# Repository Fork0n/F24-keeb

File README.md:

# F24-keeb
#### ever wished to have or use a keyboard with 2!!! function rows? no? well it's here anyways! by having 2 function rows with F13-F24 keys + 5 macro keys + 2 dials you can now have up to 19* customizable keys! that's like a built in streamdeck! and all of that while never leaving your keyboard! 

*assuming you remap all 12 additional function keys + 5 macros + 2 dial on click

<!--  -->

## Project info:
### Format: TKL++
### Materials:
- case: matte Jet Black ABS
- (alt) case top: matte purple ABS
- plate: mate Ket Black Polyoxymethylene (POM)
- keycaps: to be decided
### Switches: Gateron PRO v3 BLACK or Gateron Smoothie Sea Salt
### Microcontroller: 3rd party Type C Pi Pico (RP2040)
### Firmware: Custom, RMK/QMK/VIAL based (WIP)
### Mounting Style: gasket mount

## Design files
available [https://github.com/Fork0n/F24-keeb/tree/main/production](here)

(source will be added later)

## Assembly 101

WIP WIP WIP WIP WIP WIP WIP WIP WIP

## Firmware 101

WIP WIP WIP WIP WIP WIP WIP WIP WIP

## CH I: the idea:
it all started when I got a new laptop with the nasty copilot key, at first i left it on seen and just occasionally missclicked it opening copilot, then i found out that power toys allow you to remap any key to any function (even virtual keys), that was great for muting myself on discord but i felt like i needed more. at approximately the same time i discovered that i can turn my laptop's numpad in a DIY streamdeck AKA macropad, that was still not enough. One time when i was watching a video by bringus studious i took a closer look at the infamous _dirty cherry keyboard_, instead of a mono top row it was doubled! taking and EVEN closer look revealed that the keyboard had the row folded instead of a double row. Anyways that was the time when a "double function row keyboard" idea was born.

## Project Updates & Devlogs
Check out our detailed progress and updates in the [DEVLOGS.md](./DEVLOGS.md)!

> <small>**Project Info & Licensing**  
> Designed by **@forkosssa** ([Contact/Portfolio](https://large-type.com/#TODO)) • Licensed under [CC BY 4.0](LICENSE).  
> *All physical derivative PCBs must retain original author branding on silkscreen layers as outlined in Section 3(a).*</small>

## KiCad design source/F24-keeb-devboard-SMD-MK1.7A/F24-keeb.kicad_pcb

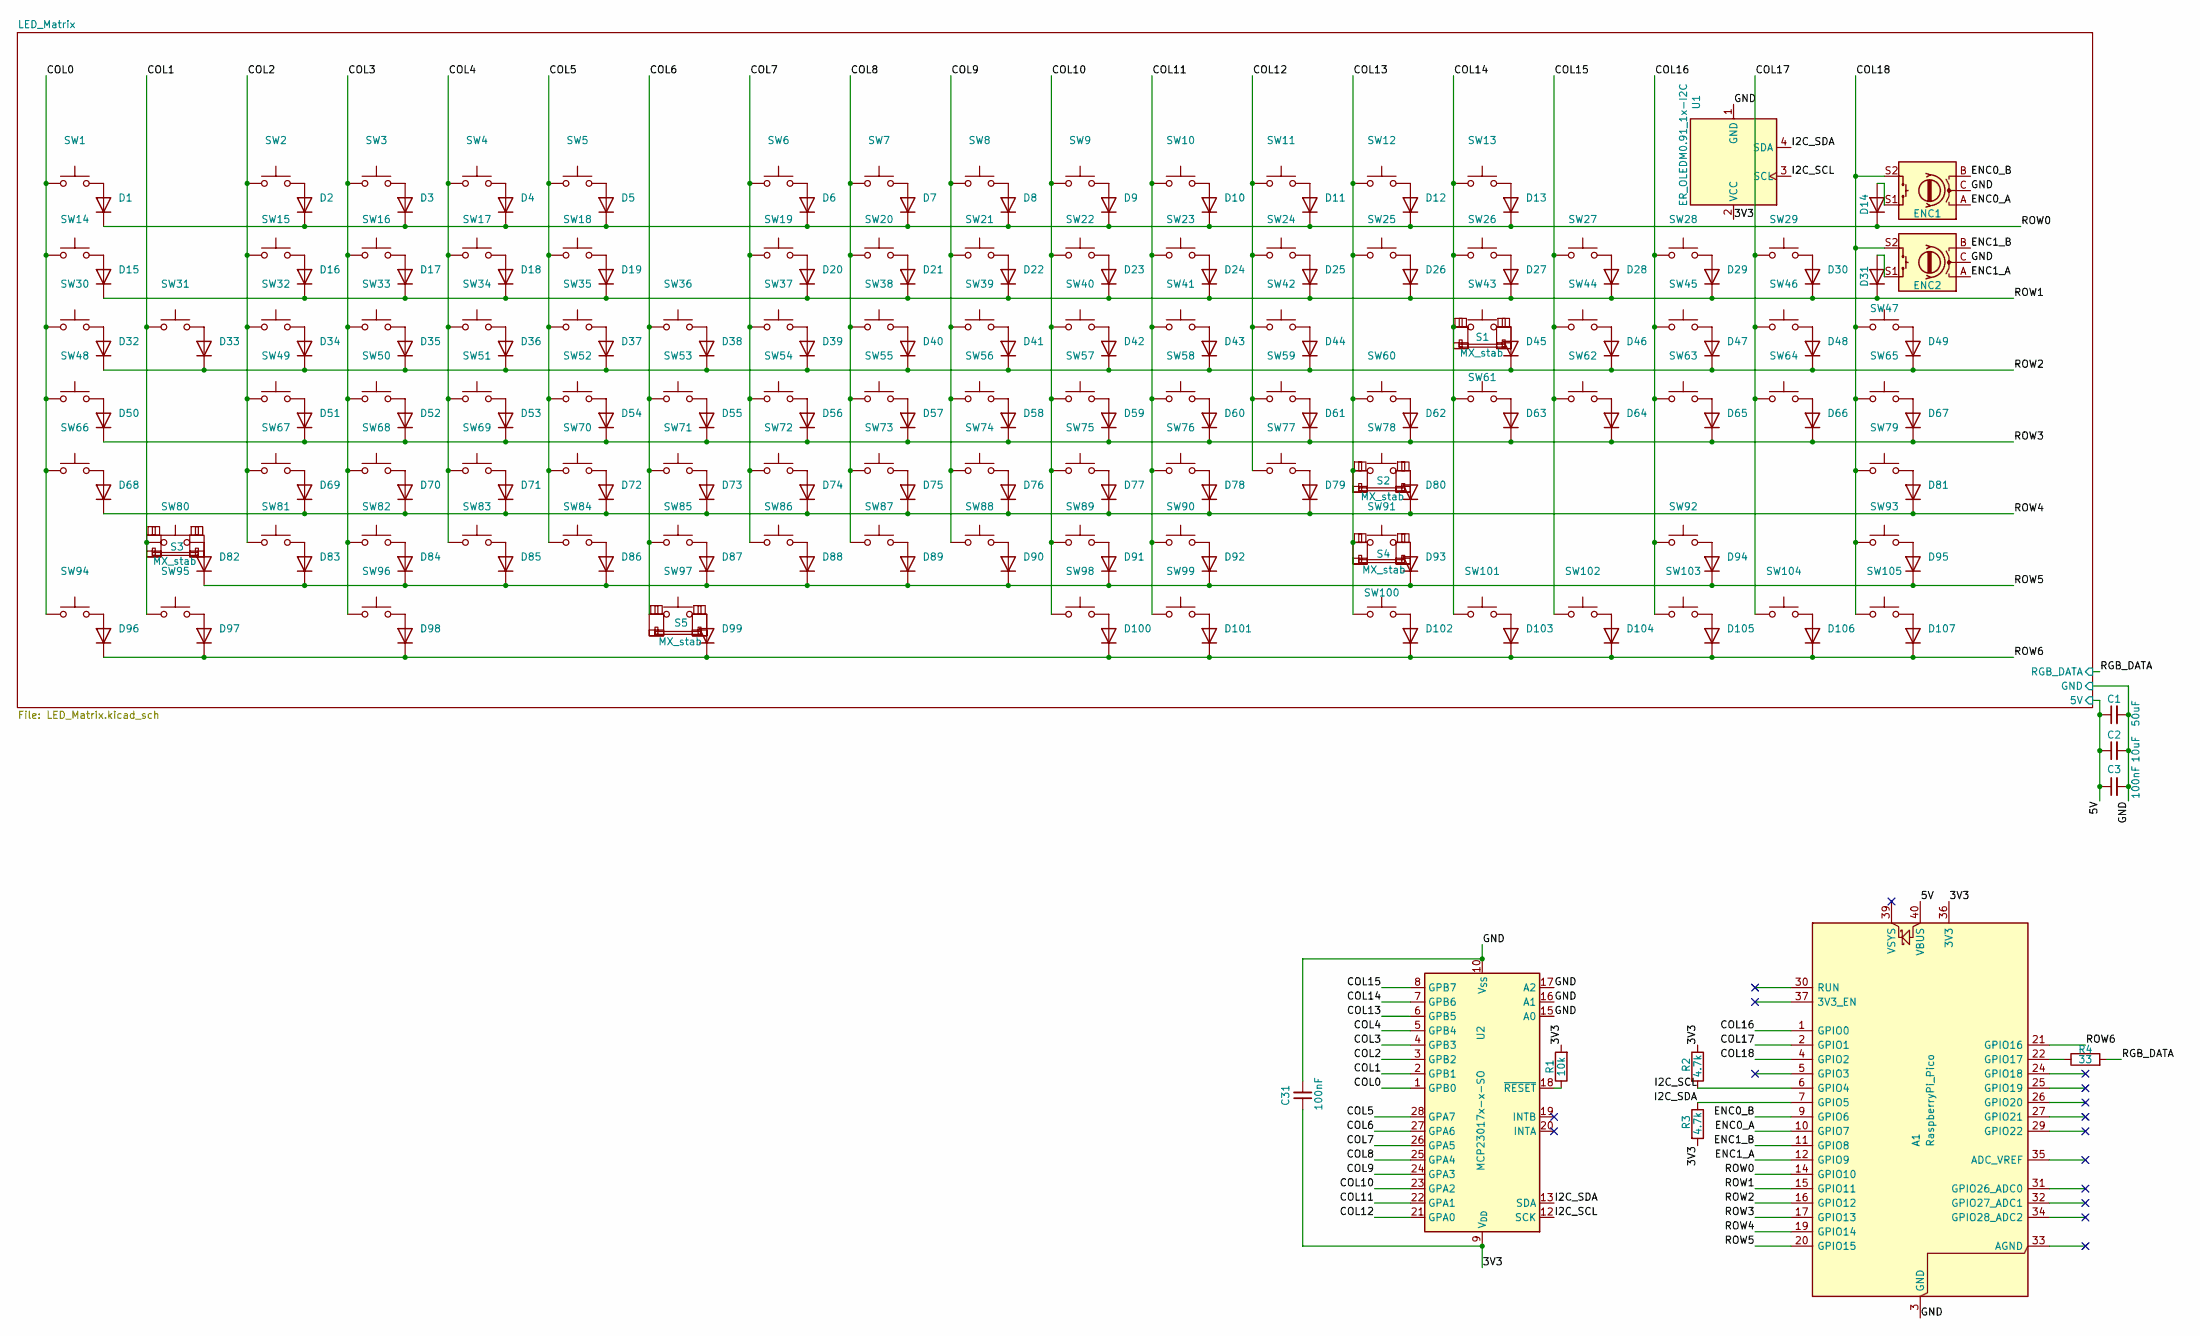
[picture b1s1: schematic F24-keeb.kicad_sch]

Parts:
A1: RaspberryPi_Pico; RaspberryPi_Pico_Common_SMD
C1: 50uF; C_0805_2012Metric
C2: 10uF; C_0805_2012Metric
C3, C31: 100nF; C_0805_2012Metric
D1, D2, D3, D4, D5, D6, D7, D8, D9, D10, D11, D12, D13, D14, D15, D16, D17, D18, D19, D20, D21, D22, D23, D24, D25, D26, D27, D28, D29, D30, D31, D32, D33, D34, D35, D36, D37, D38, D39, D40, D41, D42, D43, D44, D45, D46, D47, D48, D49, D50, D51, D52, D53, D54, D55, D56, D57, D58, D59, D60, D61, D62, D63, D64, D65, D66, D67, D68, D69, D70, D71, D72, D73, D74, D75, D76, D77, D78, D79, D80, D81, D82, D83, D84, D85, D86, D87, D88, D89, D90, D91, D92, D93, D94, D95, D96, D97, D98, D99, D100, D101, D102, D103, D104, D105, D106, D107: 1N4148; D_SOD-123F
ENC1, ENC2: RotaryEncoder_Switch; ROT_Alps_EC11E-Switch
R1: 10k; R_0805_2012Metric
R2, R3: 4.7k; R_0805_2012Metric
R4: 33; R_0805_2012Metric
S1, S2, S3: MX_stab; STAB_MX_2.25u
S4: MX_stab; STAB_MX_2.75u
S5: MX_stab; STAB_MX_P_6.25u
SW1, SW2, SW3, SW4, SW5, SW6, SW7, SW8, SW9, SW10, SW11, SW12, SW13, SW14, SW15, SW16, SW17, SW18, SW19, SW20, SW21, SW22, SW23, SW24, SW25, SW26, SW27, SW28, SW29, SW30, SW31, SW32, SW33, SW34, SW35, SW36, SW37, SW38, SW39, SW40, SW41, SW42, SW43, SW44, SW45, SW46, SW47, SW48, SW49, SW50, SW51, SW52, SW53, SW54, SW55, SW56, SW57, SW58, SW59, SW60, SW61, SW62, SW63, SW64, SW65, SW66, SW67, SW68, SW69, SW70, SW71, SW72, SW73, SW74, SW75, SW76, SW77, SW78, SW79, SW80, SW81, SW82, SW83, SW84, SW85, SW86, SW87, SW88, SW89, SW90, SW91, SW92, SW93, SW94, SW95, SW96, SW97, SW98, SW99, SW100, SW101, SW102, SW103, SW104, SW105: SW_Push; SW_Hotswap_Kailh_MX_1.00u
U1: ER_OLEDM0.91_1x-I2C
U2: MCP23017x-x-SO; SOIC-28W_7.5x17.9mm_P1.27mm

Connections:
/3V3: A1.36 (3V3), C31.1, R1.2, R2.1, R3.2, U1.2 (VCC), U2.9 (V_{DD})
/5V: A1.40 (VBUS), C1.1, C2.1, C3.1; also elsewhere on the board
/COL0: SW1.1, SW14.1, SW30.1, SW48.1, SW66.1, SW94.1, U2.1 (GPB0)
/COL1: SW31.1, SW80.1, SW95.1, U2.2 (GPB1)
/COL2: SW2.1, SW15.1, SW32.1, SW49.1, SW67.1, SW81.1, U2.3 (GPB2)
/COL3: SW3.1, SW16.1, SW33.1, SW50.1, SW68.1, SW82.1, SW96.1, U2.4 (GPB3)
/COL4: SW4.1, SW17.1, SW34.1, SW51.1, SW69.1, SW83.1, U2.5 (GPB4)
/COL5: SW5.1, SW18.1, SW35.1, SW52.1, SW70.1, SW84.1, U2.28 (GPA7)
/COL6: SW36.1, SW53.1, SW71.1, SW85.1, SW97.1, U2.27 (GPA6)
/COL7: SW6.1, SW19.1, SW37.1, SW54.1, SW72.1, SW86.1, U2.26 (GPA5)
/COL8: SW7.1, SW20.1, SW38.1, SW55.1, SW73.1, SW87.1, U2.25 (GPA4)
/COL9: SW8.1, SW21.1, SW39.1, SW56.1, SW74.1, SW88.1, U2.24 (GPA3)
/COL10: SW9.1, SW22.1, SW40.1, SW57.1, SW75.1, SW89.1, SW98.1, U2.23 (GPA2)
/COL11: SW10.1, SW23.1, SW41.1, SW58.1, SW76.1, SW90.1, SW99.1, U2.22 (GPA1)
/COL12: SW11.1, SW24.1, SW42.1, SW59.1, SW77.1, U2.21 (GPA0)
/COL13: SW12.1, SW25.1, SW60.1, SW78.1, SW91.1, SW100.1, U2.6 (GPB5)
/COL14: SW13.1, SW26.1, SW43.1, SW61.1, SW101.1, U2.7 (GPB6)
/COL15: SW27.1, SW44.1, SW62.1, SW102.1, U2.8 (GPB7)
/COL16: A1.1 (GPIO0), SW28.1, SW45.1, SW63.1, SW92.1, SW103.1
/COL17: A1.2 (GPIO1), SW29.1, SW46.1, SW64.1, SW104.1
/COL18: A1.4 (GPIO2), ENC1.S2, ENC2.S2, SW47.1, SW65.1, SW79.1, SW93.1, SW105.1
/ENC0_A: A1.10 (GPIO7), ENC1.A
/ENC0_B: A1.9 (GPIO6), ENC1.B
/ENC1_A: A1.12 (GPIO9), ENC2.A
/ENC1_B: A1.11 (GPIO8), ENC2.B
/GND: A1.3 (GND), A1.8 (GND), A1.13 (GND), A1.18 (GND), A1.23 (GND), A1.28 (GND), A1.38 (GND), C1.2, C2.2, C3.2, C31.2, ENC1.C, ENC2.C, U1.1 (GND), U2.10 (V_{SS}), U2.15 (A0), U2.16 (A1), U2.17 (A2); also elsewhere on the board
/I2C_SCL: A1.6 (GPIO4), R2.2, U1.3 (SCL), U2.12 (SCK)
/I2C_SDA: A1.7 (GPIO5), R3.1, U1.4 (SDA), U2.13 (SDA)
/RGB_DATA: R4.2; also elsewhere on the board
/ROW0: A1.14 (GPIO10), D1.1 (K), D2.1 (K), D3.1 (K), D4.1 (K), D5.1 (K), D6.1 (K), D7.1 (K), D8.1 (K), D9.1 (K), D10.1 (K), D11.1 (K), D12.1 (K), D13.1 (K), D14.1 (K)
/ROW1: A1.15 (GPIO11), D15.1 (K), D16.1 (K), D17.1 (K), D18.1 (K), D19.1 (K), D20.1 (K), D21.1 (K), D22.1 (K), D23.1 (K), D24.1 (K), D25.1 (K), D26.1 (K), D27.1 (K), D28.1 (K), D29.1 (K), D30.1 (K), D31.1 (K)
/ROW2: A1.16 (GPIO12), D32.1 (K), D33.1 (K), D34.1 (K), D35.1 (K), D36.1 (K), D37.1 (K), D38.1 (K), D39.1 (K), D40.1 (K), D41.1 (K), D42.1 (K), D43.1 (K), D44.1 (K), D45.1 (K), D46.1 (K), D47.1 (K), D48.1 (K), D49.1 (K)
/ROW3: A1.17 (GPIO13), D50.1 (K), D51.1 (K), D52.1 (K), D53.1 (K), D54.1 (K), D55.1 (K), D56.1 (K), D57.1 (K), D58.1 (K), D59.1 (K), D60.1 (K), D61.1 (K), D62.1 (K), D63.1 (K), D64.1 (K), D65.1 (K), D66.1 (K), D67.1 (K)
/ROW4: A1.19 (GPIO14), D68.1 (K), D69.1 (K), D70.1 (K), D71.1 (K), D72.1 (K), D73.1 (K), D74.1 (K), D75.1 (K), D76.1 (K), D77.1 (K), D78.1 (K), D79.1 (K), D80.1 (K), D81.1 (K)
/ROW5: A1.20 (GPIO15), D82.1 (K), D83.1 (K), D84.1 (K), D85.1 (K), D86.1 (K), D87.1 (K), D88.1 (K), D89.1 (K), D90.1 (K), D91.1 (K), D92.1 (K), D93.1 (K), D94.1 (K), D95.1 (K)
/ROW6: A1.21 (GPIO16), D96.1 (K), D97.1 (K), D98.1 (K), D99.1 (K), D100.1 (K), D101.1 (K), D102.1 (K), D103.1 (K), D104.1 (K), D105.1 (K), D106.1 (K), D107.1 (K)
unnamed: A1.22 (GPIO17), R4.1
unnamed: D1.2 (A), SW1.2
unnamed: D2.2 (A), SW2.2
unnamed: D3.2 (A), SW3.2
unnamed: D4.2 (A), SW4.2
unnamed: D5.2 (A), SW5.2
unnamed: D6.2 (A), SW6.2
unnamed: D7.2 (A), SW7.2
unnamed: D8.2 (A), SW8.2
unnamed: D9.2 (A), SW9.2
unnamed: D10.2 (A), SW10.2
unnamed: D11.2 (A), SW11.2
unnamed: D12.2 (A), SW12.2
unnamed: D13.2 (A), SW13.2
unnamed: D14.2 (A), ENC1.S1
unnamed: D15.2 (A), SW14.2
unnamed: D16.2 (A), SW15.2
unnamed: D17.2 (A), SW16.2
unnamed: D18.2 (A), SW17.2
unnamed: D19.2 (A), SW18.2
unnamed: D20.2 (A), SW19.2
unnamed: D21.2 (A), SW20.2
unnamed: D22.2 (A), SW21.2
unnamed: D23.2 (A), SW22.2
unnamed: D24.2 (A), SW23.2
unnamed: D25.2 (A), SW24.2
unnamed: D26.2 (A), SW25.2
unnamed: D27.2 (A), SW26.2
unnamed: D28.2 (A), SW27.2
unnamed: D29.2 (A), SW28.2
unnamed: D30.2 (A), SW29.2
unnamed: D31.2 (A), ENC2.S1
unnamed: D32.2 (A), SW30.2
unnamed: D33.2 (A), SW31.2
unnamed: D34.2 (A), SW32.2
unnamed: D35.2 (A), SW33.2
unnamed: D36.2 (A), SW34.2
unnamed: D37.2 (A), SW35.2
unnamed: D38.2 (A), SW36.2
unnamed: D39.2 (A), SW37.2
unnamed: D40.2 (A), SW38.2
unnamed: D41.2 (A), SW39.2
unnamed: D42.2 (A), SW40.2
unnamed: D43.2 (A), SW41.2
unnamed: D44.2 (A), SW42.2
unnamed: D45.2 (A), SW43.2
unnamed: D46.2 (A), SW44.2
unnamed: D47.2 (A), SW45.2
unnamed: D48.2 (A), SW46.2
unnamed: D49.2 (A), SW47.2
unnamed: D50.2 (A), SW48.2
unnamed: D51.2 (A), SW49.2
unnamed: D52.2 (A), SW50.2
unnamed: D53.2 (A), SW51.2
unnamed: D54.2 (A), SW52.2
unnamed: D55.2 (A), SW53.2
unnamed: D56.2 (A), SW54.2
unnamed: D57.2 (A), SW55.2
unnamed: D58.2 (A), SW56.2
unnamed: D59.2 (A), SW57.2
unnamed: D60.2 (A), SW58.2
unnamed: D61.2 (A), SW59.2
unnamed: D62.2 (A), SW60.2
unnamed: D63.2 (A), SW61.2
unnamed: D64.2 (A), SW62.2
unnamed: D65.2 (A), SW63.2
unnamed: D66.2 (A), SW64.2
unnamed: D67.2 (A), SW65.2
unnamed: D68.2 (A), SW66.2
unnamed: D69.2 (A), SW67.2
unnamed: D70.2 (A), SW68.2
unnamed: D71.2 (A), SW69.2
unnamed: D72.2 (A), SW70.2
unnamed: D73.2 (A), SW71.2
unnamed: D74.2 (A), SW72.2
unnamed: D75.2 (A), SW73.2
unnamed: D76.2 (A), SW74.2
unnamed: D77.2 (A), SW75.2
unnamed: D78.2 (A), SW76.2
unnamed: D79.2 (A), SW77.2
unnamed: D80.2 (A), SW78.2
unnamed: D81.2 (A), SW79.2
unnamed: D82.2 (A), SW80.2
unnamed: D83.2 (A), SW81.2
unnamed: D84.2 (A), SW82.2
unnamed: D85.2 (A), SW83.2
unnamed: D86.2 (A), SW84.2
unnamed: D87.2 (A), SW85.2
unnamed: D88.2 (A), SW86.2
unnamed: D89.2 (A), SW87.2
unnamed: D90.2 (A), SW88.2
unnamed: D91.2 (A), SW89.2
unnamed: D92.2 (A), SW90.2
unnamed: D93.2 (A), SW91.2
unnamed: D94.2 (A), SW92.2
unnamed: D95.2 (A), SW93.2
unnamed: D96.2 (A), SW94.2
unnamed: D97.2 (A), SW95.2
unnamed: D98.2 (A), SW96.2
unnamed: D99.2 (A), SW97.2
unnamed: D100.2 (A), SW98.2
unnamed: D101.2 (A), SW99.2
unnamed: D102.2 (A), SW100.2
unnamed: D103.2 (A), SW101.2
unnamed: D104.2 (A), SW102.2
unnamed: D105.2 (A), SW103.2
unnamed: D106.2 (A), SW104.2
unnamed: D107.2 (A), SW105.2
unnamed: R1.1, U2.18 (~RESET)

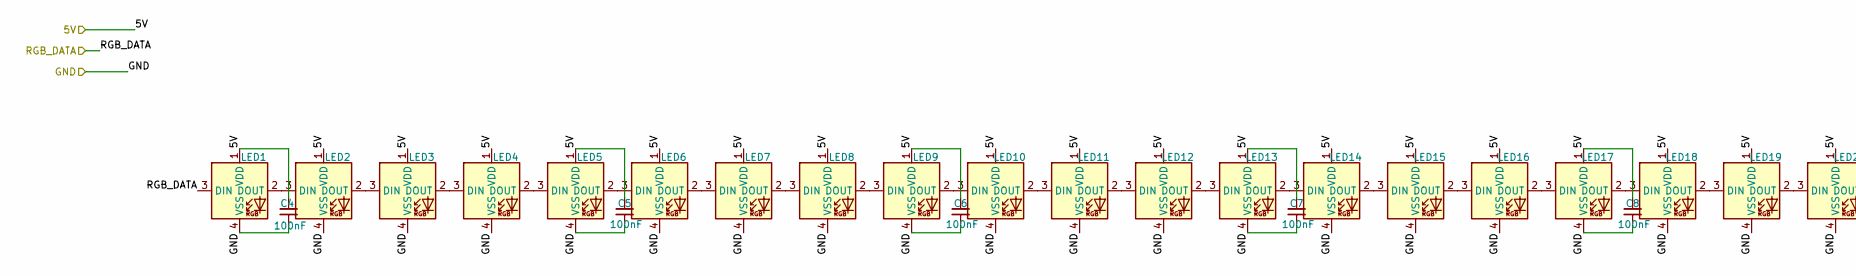
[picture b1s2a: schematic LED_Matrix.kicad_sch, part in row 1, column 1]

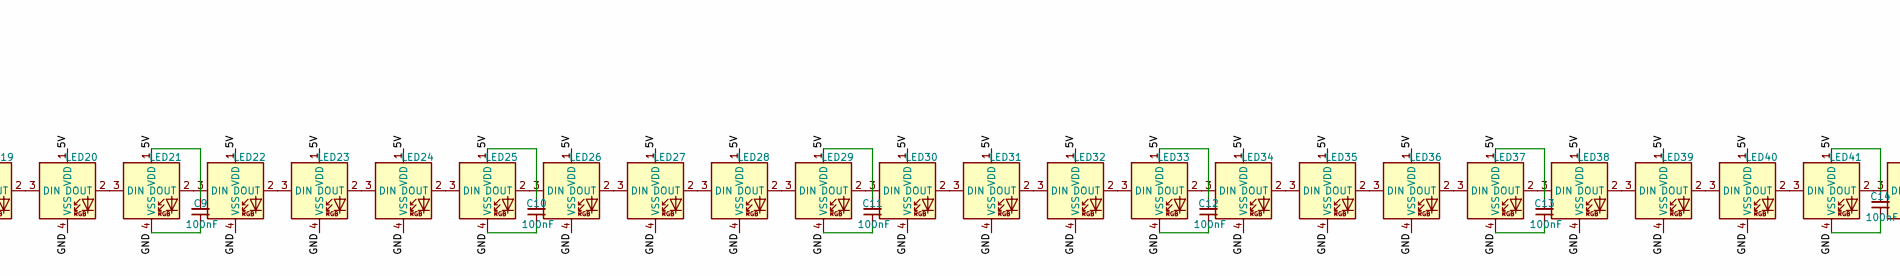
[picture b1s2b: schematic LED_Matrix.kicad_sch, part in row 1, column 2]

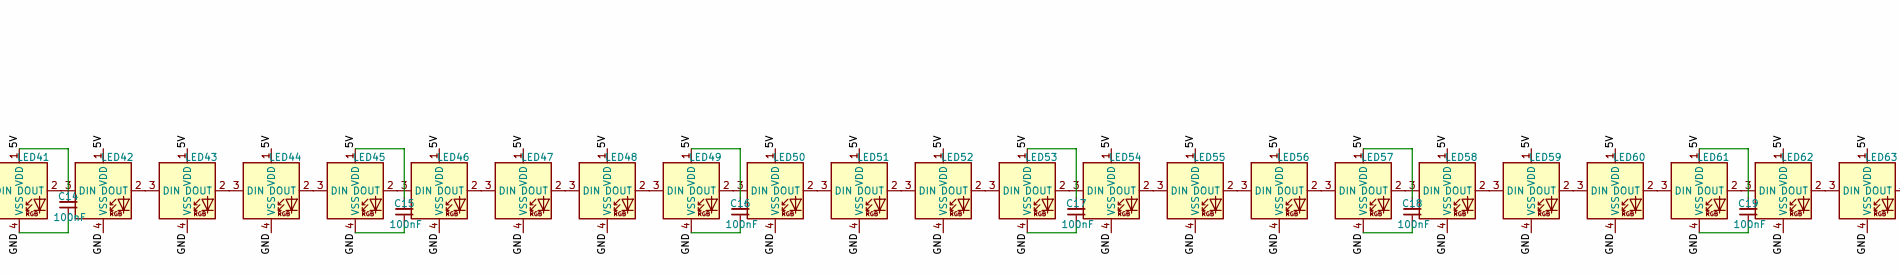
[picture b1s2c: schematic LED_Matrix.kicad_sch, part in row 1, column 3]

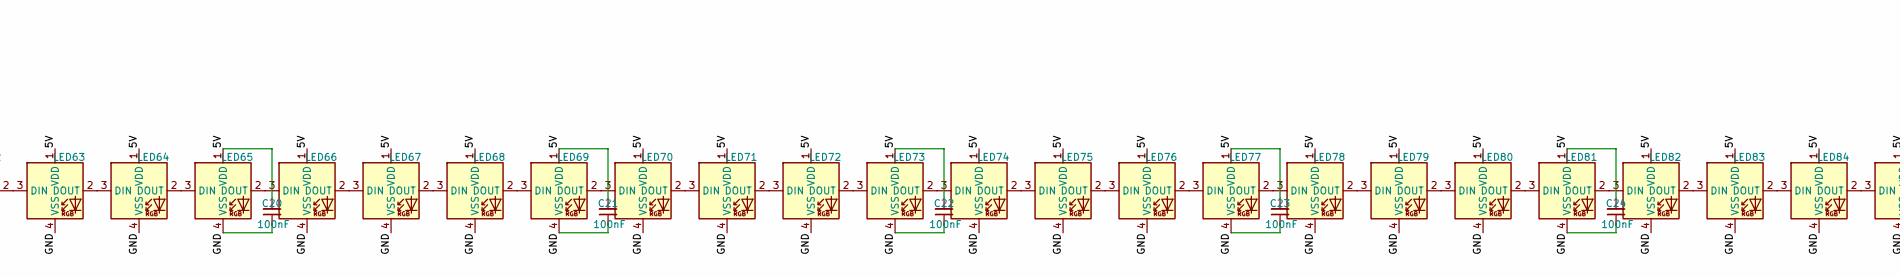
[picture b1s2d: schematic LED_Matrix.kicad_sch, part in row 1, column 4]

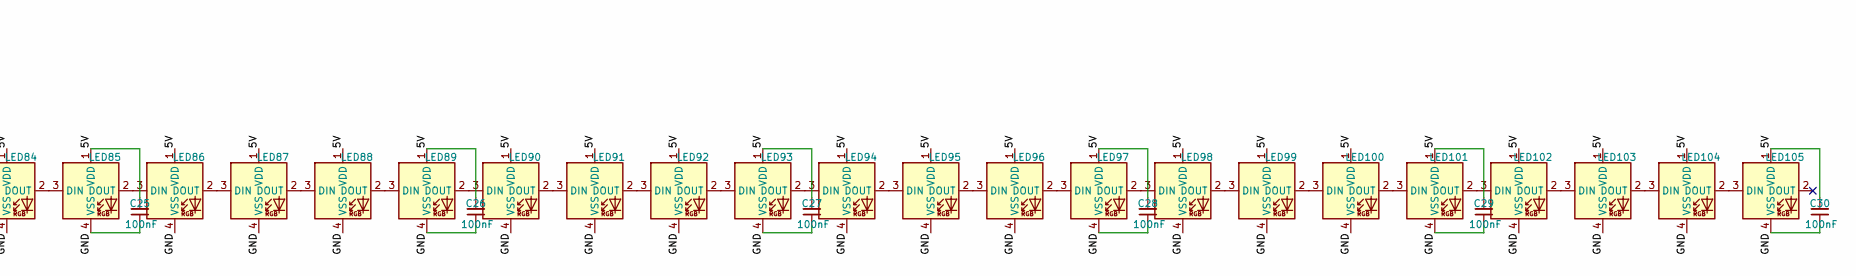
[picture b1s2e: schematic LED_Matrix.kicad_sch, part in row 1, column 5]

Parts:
C4, C5, C6, C7, C8, C9, C10, C11, C12, C13, C14, C15, C16, C17, C18, C19, C20, C21, C22, C23, C24, C25, C26, C27, C28, C29, C30: 100nF; C_0805_2012Metric
LED1, LED2, LED3, LED4, LED5, LED6, LED7, LED8, LED9, LED10, LED11, LED12, LED13, LED14, LED15, LED16, LED17, LED18, LED19, LED20, LED21, LED22, LED23, LED24, LED25, LED26, LED27, LED28, LED29, LED30, LED31, LED32, LED33, LED34, LED35, LED36, LED37, LED38, LED39, LED40, LED41, LED42, LED43, LED44, LED45, LED46, LED47, LED48, LED49, LED50, LED51, LED52, LED53, LED54, LED55, LED56, LED57, LED58, LED59, LED60, LED61, LED62, LED63, LED64, LED65, LED66, LED67, LED68, LED69, LED70, LED71, LED72, LED73, LED74, LED75, LED76, LED77, LED78, LED79, LED80, LED81, LED82, LED83, LED84, LED85, LED86, LED87, LED88, LED89, LED90, LED91, LED92, LED93, LED94, LED95, LED96, LED97, LED98, LED99, LED100, LED101, LED102, LED103, LED104, LED105: MX_SK6812MINI-E; LED_SK6812MINI-E_3.2x2.8mm_P1.5mm_ReverseMount

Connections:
/5V: C4.2, C5.2, C6.2, C7.2, C8.2, C9.2, C10.2, C11.2, C12.2, C13.2, C14.2, C15.2, C16.2, C17.2, C18.2, C19.2, C20.2, C21.2, C22.2, C23.2, C24.2, C25.2, C26.2, C27.2, C28.2, C29.2, C30.2, LED1.1 (VDD), LED2.1 (VDD), LED3.1 (VDD), LED4.1 (VDD), LED5.1 (VDD), LED6.1 (VDD), LED7.1 (VDD), LED8.1 (VDD), LED9.1 (VDD), LED10.1 (VDD), LED11.1 (VDD), LED12.1 (VDD), LED13.1 (VDD), LED14.1 (VDD), LED15.1 (VDD), LED16.1 (VDD), LED17.1 (VDD), LED18.1 (VDD), LED19.1 (VDD), LED20.1 (VDD), LED21.1 (VDD), LED22.1 (VDD), LED23.1 (VDD), LED24.1 (VDD), LED25.1 (VDD), LED26.1 (VDD), LED27.1 (VDD), LED28.1 (VDD), LED29.1 (VDD), LED30.1 (VDD), LED31.1 (VDD), LED32.1 (VDD), LED33.1 (VDD), LED34.1 (VDD), LED35.1 (VDD), LED36.1 (VDD), LED37.1 (VDD), LED38.1 (VDD), LED39.1 (VDD), LED40.1 (VDD), LED41.1 (VDD), LED42.1 (VDD), LED43.1 (VDD), LED44.1 (VDD), LED45.1 (VDD), LED46.1 (VDD), LED47.1 (VDD), LED48.1 (VDD), LED49.1 (VDD), LED50.1 (VDD), LED51.1 (VDD), LED52.1 (VDD), LED53.1 (VDD), LED54.1 (VDD), LED55.1 (VDD), LED56.1 (VDD), LED57.1 (VDD), LED58.1 (VDD), LED59.1 (VDD), LED60.1 (VDD), LED61.1 (VDD), LED62.1 (VDD), LED63.1 (VDD), LED64.1 (VDD), LED65.1 (VDD), LED66.1 (VDD), LED67.1 (VDD), LED68.1 (VDD), LED69.1 (VDD), LED70.1 (VDD), LED71.1 (VDD), LED72.1 (VDD), LED73.1 (VDD), LED74.1 (VDD), LED75.1 (VDD), LED76.1 (VDD), LED77.1 (VDD), LED78.1 (VDD), LED79.1 (VDD), LED80.1 (VDD), LED81.1 (VDD), LED82.1 (VDD), LED83.1 (VDD), LED84.1 (VDD), LED85.1 (VDD), LED86.1 (VDD), LED87.1 (VDD), LED88.1 (VDD), LED89.1 (VDD), LED90.1 (VDD), LED91.1 (VDD), LED92.1 (VDD), LED93.1 (VDD), LED94.1 (VDD), LED95.1 (VDD), LED96.1 (VDD), LED97.1 (VDD), LED98.1 (VDD), LED99.1 (VDD), LED100.1 (VDD), LED101.1 (VDD), LED102.1 (VDD), LED103.1 (VDD), LED104.1 (VDD), LED105.1 (VDD); also elsewhere on the board
/GND: C4.1, C5.1, C6.1, C7.1, C8.1, C9.1, C10.1, C11.1, C12.1, C13.1, C14.1, C15.1, C16.1, C17.1, C18.1, C19.1, C20.1, C21.1, C22.1, C23.1, C24.1, C25.1, C26.1, C27.1, C28.1, C29.1, C30.1, LED1.4 (VSS), LED2.4 (VSS), LED3.4 (VSS), LED4.4 (VSS), LED5.4 (VSS), LED6.4 (VSS), LED7.4 (VSS), LED8.4 (VSS), LED9.4 (VSS), LED10.4 (VSS), LED11.4 (VSS), LED12.4 (VSS), LED13.4 (VSS), LED14.4 (VSS), LED15.4 (VSS), LED16.4 (VSS), LED17.4 (VSS), LED18.4 (VSS), LED19.4 (VSS), LED20.4 (VSS), LED21.4 (VSS), LED22.4 (VSS), LED23.4 (VSS), LED24.4 (VSS), LED25.4 (VSS), LED26.4 (VSS), LED27.4 (VSS), LED28.4 (VSS), LED29.4 (VSS), LED30.4 (VSS), LED31.4 (VSS), LED32.4 (VSS), LED33.4 (VSS), LED34.4 (VSS), LED35.4 (VSS), LED36.4 (VSS), LED37.4 (VSS), LED38.4 (VSS), LED39.4 (VSS), LED40.4 (VSS), LED41.4 (VSS), LED42.4 (VSS), LED43.4 (VSS), LED44.4 (VSS), LED45.4 (VSS), LED46.4 (VSS), LED47.4 (VSS), LED48.4 (VSS), LED49.4 (VSS), LED50.4 (VSS), LED51.4 (VSS), LED52.4 (VSS), LED53.4 (VSS), LED54.4 (VSS), LED55.4 (VSS), LED56.4 (VSS), LED57.4 (VSS), LED58.4 (VSS), LED59.4 (VSS), LED60.4 (VSS), LED61.4 (VSS), LED62.4 (VSS), LED63.4 (VSS), LED64.4 (VSS), LED65.4 (VSS), LED66.4 (VSS), LED67.4 (VSS), LED68.4 (VSS), LED69.4 (VSS), LED70.4 (VSS), LED71.4 (VSS), LED72.4 (VSS), LED73.4 (VSS), LED74.4 (VSS), LED75.4 (VSS), LED76.4 (VSS), LED77.4 (VSS), LED78.4 (VSS), LED79.4 (VSS), LED80.4 (VSS), LED81.4 (VSS), LED82.4 (VSS), LED83.4 (VSS), LED84.4 (VSS), LED85.4 (VSS), LED86.4 (VSS), LED87.4 (VSS), LED88.4 (VSS), LED89.4 (VSS), LED90.4 (VSS), LED91.4 (VSS), LED92.4 (VSS), LED93.4 (VSS), LED94.4 (VSS), LED95.4 (VSS), LED96.4 (VSS), LED97.4 (VSS), LED98.4 (VSS), LED99.4 (VSS), LED100.4 (VSS), LED101.4 (VSS), LED102.4 (VSS), LED103.4 (VSS), LED104.4 (VSS), LED105.4 (VSS); also elsewhere on the board
/RGB_DATA: LED1.3 (DIN); also elsewhere on the board
unnamed: LED1.2 (DOUT), LED2.3 (DIN)
unnamed: LED2.2 (DOUT), LED3.3 (DIN)
unnamed: LED3.2 (DOUT), LED4.3 (DIN)
unnamed: LED4.2 (DOUT), LED5.3 (DIN)
unnamed: LED5.2 (DOUT), LED6.3 (DIN)
unnamed: LED6.2 (DOUT), LED7.3 (DIN)
unnamed: LED7.2 (DOUT), LED8.3 (DIN)
unnamed: LED8.2 (DOUT), LED9.3 (DIN)
unnamed: LED9.2 (DOUT), LED10.3 (DIN)
unnamed: LED10.2 (DOUT), LED11.3 (DIN)
unnamed: LED11.2 (DOUT), LED12.3 (DIN)
unnamed: LED12.2 (DOUT), LED13.3 (DIN)
unnamed: LED13.2 (DOUT), LED14.3 (DIN)
unnamed: LED14.2 (DOUT), LED15.3 (DIN)
unnamed: LED15.2 (DOUT), LED16.3 (DIN)
unnamed: LED16.2 (DOUT), LED17.3 (DIN)
unnamed: LED17.2 (DOUT), LED18.3 (DIN)
unnamed: LED18.2 (DOUT), LED19.3 (DIN)
unnamed: LED19.2 (DOUT), LED20.3 (DIN)
unnamed: LED20.2 (DOUT), LED21.3 (DIN)
unnamed: LED21.2 (DOUT), LED22.3 (DIN)
unnamed: LED22.2 (DOUT), LED23.3 (DIN)
unnamed: LED23.2 (DOUT), LED24.3 (DIN)
unnamed: LED24.2 (DOUT), LED25.3 (DIN)
unnamed: LED25.2 (DOUT), LED26.3 (DIN)
unnamed: LED26.2 (DOUT), LED27.3 (DIN)
unnamed: LED27.2 (DOUT), LED28.3 (DIN)
unnamed: LED28.2 (DOUT), LED29.3 (DIN)
unnamed: LED29.2 (DOUT), LED30.3 (DIN)
unnamed: LED30.2 (DOUT), LED31.3 (DIN)
unnamed: LED31.2 (DOUT), LED32.3 (DIN)
unnamed: LED32.2 (DOUT), LED33.3 (DIN)
unnamed: LED33.2 (DOUT), LED34.3 (DIN)
unnamed: LED34.2 (DOUT), LED35.3 (DIN)
unnamed: LED35.2 (DOUT), LED36.3 (DIN)
unnamed: LED36.2 (DOUT), LED37.3 (DIN)
unnamed: LED37.2 (DOUT), LED38.3 (DIN)
unnamed: LED38.2 (DOUT), LED39.3 (DIN)
unnamed: LED39.2 (DOUT), LED40.3 (DIN)
unnamed: LED40.2 (DOUT), LED41.3 (DIN)
unnamed: LED41.2 (DOUT), LED42.3 (DIN)
unnamed: LED42.2 (DOUT), LED43.3 (DIN)
unnamed: LED43.2 (DOUT), LED44.3 (DIN)
unnamed: LED44.2 (DOUT), LED45.3 (DIN)
unnamed: LED45.2 (DOUT), LED46.3 (DIN)
unnamed: LED46.2 (DOUT), LED47.3 (DIN)
unnamed: LED47.2 (DOUT), LED48.3 (DIN)
unnamed: LED48.2 (DOUT), LED49.3 (DIN)
unnamed: LED49.2 (DOUT), LED50.3 (DIN)
unnamed: LED50.2 (DOUT), LED51.3 (DIN)
unnamed: LED51.2 (DOUT), LED52.3 (DIN)
unnamed: LED52.2 (DOUT), LED53.3 (DIN)
unnamed: LED53.2 (DOUT), LED54.3 (DIN)
unnamed: LED54.2 (DOUT), LED55.3 (DIN)
unnamed: LED55.2 (DOUT), LED56.3 (DIN)
unnamed: LED56.2 (DOUT), LED57.3 (DIN)
unnamed: LED57.2 (DOUT), LED58.3 (DIN)
unnamed: LED58.2 (DOUT), LED59.3 (DIN)
unnamed: LED59.2 (DOUT), LED60.3 (DIN)
unnamed: LED60.2 (DOUT), LED61.3 (DIN)
unnamed: LED61.2 (DOUT), LED62.3 (DIN)
unnamed: LED62.2 (DOUT), LED63.3 (DIN)
unnamed: LED63.2 (DOUT), LED64.3 (DIN)
unnamed: LED64.2 (DOUT), LED65.3 (DIN)
unnamed: LED65.2 (DOUT), LED66.3 (DIN)
unnamed: LED66.2 (DOUT), LED67.3 (DIN)
unnamed: LED67.2 (DOUT), LED68.3 (DIN)
unnamed: LED68.2 (DOUT), LED69.3 (DIN)
unnamed: LED69.2 (DOUT), LED70.3 (DIN)
unnamed: LED70.2 (DOUT), LED71.3 (DIN)
unnamed: LED71.2 (DOUT), LED72.3 (DIN)
unnamed: LED72.2 (DOUT), LED73.3 (DIN)
unnamed: LED73.2 (DOUT), LED74.3 (DIN)
unnamed: LED74.2 (DOUT), LED75.3 (DIN)
unnamed: LED75.2 (DOUT), LED76.3 (DIN)
unnamed: LED76.2 (DOUT), LED77.3 (DIN)
unnamed: LED77.2 (DOUT), LED78.3 (DIN)
unnamed: LED78.2 (DOUT), LED79.3 (DIN)
unnamed: LED79.2 (DOUT), LED80.3 (DIN)
unnamed: LED80.2 (DOUT), LED81.3 (DIN)
unnamed: LED81.2 (DOUT), LED82.3 (DIN)
unnamed: LED82.2 (DOUT), LED83.3 (DIN)
unnamed: LED83.2 (DOUT), LED84.3 (DIN)
unnamed: LED84.2 (DOUT), LED85.3 (DIN)
unnamed: LED85.2 (DOUT), LED86.3 (DIN)
unnamed: LED86.2 (DOUT), LED87.3 (DIN)
unnamed: LED87.2 (DOUT), LED88.3 (DIN)
unnamed: LED88.2 (DOUT), LED89.3 (DIN)
unnamed: LED89.2 (DOUT), LED90.3 (DIN)
unnamed: LED90.2 (DOUT), LED91.3 (DIN)
unnamed: LED91.2 (DOUT), LED92.3 (DIN)
unnamed: LED92.2 (DOUT), LED93.3 (DIN)
unnamed: LED93.2 (DOUT), LED94.3 (DIN)
unnamed: LED94.2 (DOUT), LED95.3 (DIN)
unnamed: LED95.2 (DOUT), LED96.3 (DIN)
unnamed: LED96.2 (DOUT), LED97.3 (DIN)
unnamed: LED97.2 (DOUT), LED98.3 (DIN)
unnamed: LED98.2 (DOUT), LED99.3 (DIN)
unnamed: LED99.2 (DOUT), LED100.3 (DIN)
unnamed: LED100.2 (DOUT), LED101.3 (DIN)
unnamed: LED101.2 (DOUT), LED102.3 (DIN)
unnamed: LED102.2 (DOUT), LED103.3 (DIN)
unnamed: LED103.2 (DOUT), LED104.3 (DIN)
unnamed: LED104.2 (DOUT), LED105.3 (DIN)

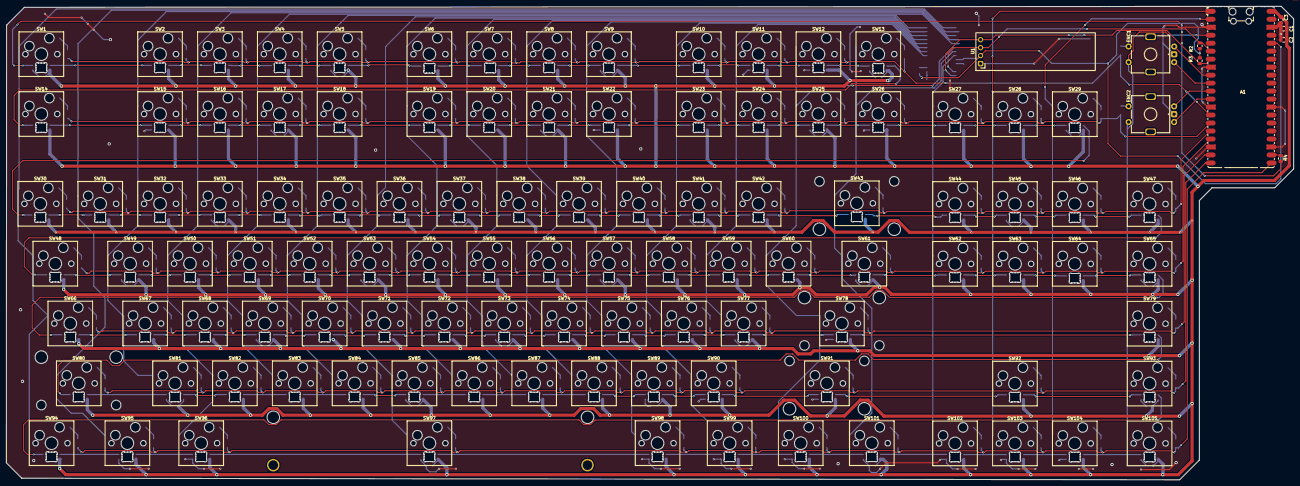
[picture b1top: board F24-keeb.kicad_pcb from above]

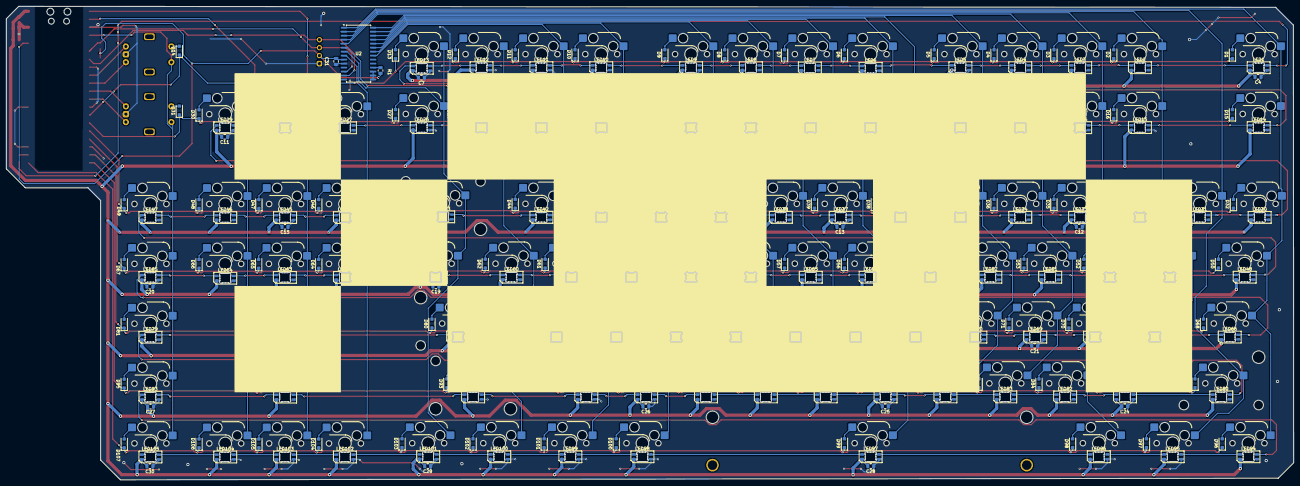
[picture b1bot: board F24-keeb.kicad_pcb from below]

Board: 2 copper layers, 409.7 x 150.7 mm, 362 parts (242 on the bottom side), 249 nets.

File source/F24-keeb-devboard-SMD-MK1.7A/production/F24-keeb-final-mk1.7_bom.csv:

Designator,Footprint,Quantity,Value,LCSC Part #
A1,RaspberryPi_Pico_Common_SMD,1,RaspberryPi_Pico,
C1,0805,1,50uF,
"C10, C11, C12, C13, C14, C15, C16, C17, C18, C19, C20, C21, C22, C23, C24, C25, C26, C27, C28, C29, C3, C30, C31, C4, C5, C6, C7, C8, C9",0805,29,100nF,
C2,0805,1,10uF,
"D1, D10, D100, D101, D102, D103, D104, D105, D106, D107, D11, D12, D13, D14, D15, D16, D17, D18, D19, D2, D20, D21, D22, D23, D24, D25, D26, D27, D28, D29, D3, D30, D31, D32, D33, D34, D35, D36, D37, D38, D39, D4, D40, D41, D42, D43, D44, D45, D46, D47, D48, D49, D5, D50, D51, D52, D53, D54, D55, D56, D57, D58, D59, D6, D60, D61, D62, D63, D64, D65, D66, D67, D68, D69, D7, D70, D71, D72, D73, D74, D75, D76, D77, D78, D79, D8, D80, D81, D82, D83, D84, D85, D86, D87, D88, D89, D9, D90, D91, D92, D93, D94, D95, D96, D97, D98, D99",D_SOD-123F,107,1N4148,
"ENC1, ENC2",ROT_Alps_EC11E-Switch,2,RotaryEncoder_Switch,
"LED1, LED10, LED100, LED101, LED102, LED103, LED104, LED105, LED11, LED12, LED13, LED14, LED15, LED16, LED17, LED18, LED19, LED2, LED20, LED21, LED22, LED23, LED24, LED25, LED26, LED27, LED28, LED29, LED3, LED30, LED31, LED32, LED33, LED34, LED35, LED36, LED37, LED38, LED39, LED4, LED40, LED41, LED42, LED43, LED44, LED45, LED46, LED47, LED48, LED49, LED5, LED50, LED51, LED52, LED53, LED54, LED55, LED56, LED57, LED58, LED59, LED6, LED60, LED61, LED62, LED63, LED64, LED65, LED66, LED67, LED68, LED69, LED7, LED70, LED71, LED72, LED73, LED74, LED75, LED76, LED77, LED78, LED79, LED8, LED80, LED81, LED82, LED83, LED84, LED85, LED86, LED87, LED88, LED89, LED9, LED90, LED91, LED92, LED93, LED94, LED95, LED96, LED97, LED98, LED99",LED_SK6812MINI-E_3.2x2.8mm_P1.5mm_ReverseMount,105,MX_SK6812MINI-E,
R1,0805,1,10k,
"R2, R3",0805,2,4.7k,
R4,0805,1,33,
"S1, S2, S3",STAB_MX_2.25u,3,MX_stab,
S4,STAB_MX_2.75u,1,MX_stab,
S5,STAB_MX_P_6.25u,1,MX_stab,
"SW1, SW10, SW100, SW101, SW102, SW103, SW104, SW105, SW11, SW12, SW13, SW14, SW15, SW16, SW17, SW18, SW19, SW2, SW20, SW21, SW22, SW23, SW24, SW25, SW26, SW27, SW28, SW29, SW3, SW30, SW31, SW32, SW33, SW34, SW35, SW36, SW37, SW38, SW39, SW4, SW40, SW41, SW42, SW43, SW44, SW45, SW46, SW47, SW48, SW49, SW5, SW50, SW51, SW52, SW53, SW54, SW55, SW56, SW57, SW58, SW59, SW6, SW60, SW61, SW62, SW63, SW64, SW65, SW66, SW67, SW68, SW69, SW7, SW70, SW71, SW72, SW73, SW74, SW75, SW76, SW77, SW78, SW79, SW8, SW80, SW81, SW82, SW83, SW84, SW85, SW86, SW87, SW88, SW89, SW9, SW90, SW91, SW92, SW93, SW94, SW95, SW96, SW97, SW98, SW99",SW_Hotswap_Kailh_MX_1.00u,105,SW_Push,
U1,ER_OLEDM0.91_1x-I2C,1,ER_OLEDM0.91_1x-I2C,
U2,SOIC-28W_7.5x17.9mm_P1.27mm,1,MCP23017x-x-SO,
